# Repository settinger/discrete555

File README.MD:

# VS555

## A 555-style timer made of discrete components, DIP-8 size

Evil Mad Scientist Labs famously [scaled up the 555 timer](https://shop.evilmadscientist.com/productsmenu/652), splitting it into discrete parts. Can it be scaled back down to DIP-8 size, but keeping the discrete parts?

Albert van Dalen created a [wager to shrinkify EMSL's discrete 741 op-amp](https://www.avdweb.nl/div/misc2/discrete-741-operational-amplifier-in-dil8). Additional info on [hackaday.io](https://hackaday.io/project/177194-discrete-741-operational-amplifier-in-dil8). My approach to that challenge is [here](https://github.com/settinger/discrete741). It seemed only natural to extend it to EMSL's 555 kit, also!

The discrete 555 IC has 6 more transistors than the discrete 741 IC, so I didn't even try for a one-sided component layout. I had to use 4 layers, as well. The BJTs are in the SOT-883L package (1.0mm by 0.6mm, a wee bit wider than an 0402 component). There are probably some more space savings to be gained by finding a cleverer part arrangement and by switching from KiCad's 0201 footprint to a more compact 0201 footprint.

TODO: Re-check design, order boards and parts if I'm feeling brave, order stencil if I'm not feeling _that_ brave, figure out how a nifty demo.

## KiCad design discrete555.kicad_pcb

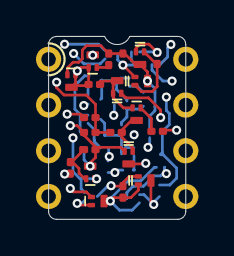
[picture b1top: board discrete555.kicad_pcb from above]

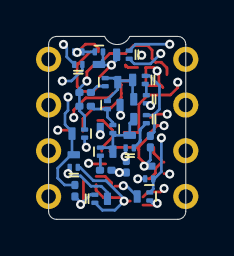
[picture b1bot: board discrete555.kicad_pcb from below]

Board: 4 copper layers, 7.6 x 10.2 mm, 44 parts (22 on the bottom side), 33 nets.

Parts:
J1: DIP-8; DIP-8_W7.62mm
Q1, Q2, Q3, Q4, Q14, Q15, Q16, Q17, Q18, Q20, Q21, Q22, Q24: CET3904E; SOT-883L-alt
Q5, Q6, Q7, Q8, Q9, Q10, Q11, Q12, Q13, Q23, Q25, Q191, Q192: CET3906E; SOT-883L
R1, R3, R7, R8, R9, R11, R15: 4.7kΩ; R_0201_0603Metric
R2: 820Ω; R_0201_0603Metric
R4: 1kΩ; R_0201_0603Metric
R5: 10kΩ; R_0201_0603Metric
R6, R17: 100kΩ; R_0201_0603Metric
R10: 15kΩ; R_0201_0603Metric
R12: 6.8kΩ; R_0201_0603Metric
R13: 3.9kΩ; R_0201_0603Metric
R14: 220Ω; R_0201_0603Metric
R16: 100Ω; R_0201_0603Metric

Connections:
CTRL: J1.5, Q4.1, R7.2, R8.1
DIS: J1.7, Q14.3
GND: J1.1, Q7.3, Q10.3, Q12.3, Q13.3, Q14.2, Q15.2, Q16.2, Q17.2, Q24.2, R5.2, R6.2, R9.2, R15.2
unnamed: Q1.2, Q2.1
unnamed: Q1.3, Q2.3, Q5.1, Q5.3, Q6.1
unnamed: Q2.2, Q3.2, R5.1
unnamed: Q3.1, Q4.2
unnamed: Q3.3, Q4.3, Q7.1, Q8.1, Q8.3
unnamed: Q5.2, R1.2
unnamed: Q6.2, Q7.2, R2.2
unnamed: Q8.2, R3.2
unnamed: Q9.2, R4.2
unnamed: Q10.2, Q11.1
unnamed: Q9.3, Q11.2, Q12.2
unnamed: Q11.3, Q15.1, R6.1
unnamed: Q12.1, Q13.2
unnamed: Q13.1, R8.2, R9.1
unnamed: Q14.1, Q25.3, R16.2
unnamed: Q6.3, Q15.3, Q16.1, R11.2
unnamed: Q16.3, Q17.1, Q18.2
unnamed: Q17.3, Q20.1, Q191.3, R11.1
unnamed: Q18.1, Q18.3, Q25.2, R10.2
unnamed: Q20.2, R14.2, R15.1, R16.1
unnamed: Q20.3, Q21.1, Q23.1, Q23.3, R12.1
unnamed: Q21.2, Q22.1, R13.2
unnamed: Q24.1, R14.1
unnamed: Q25.1, R17.2
unnamed: Q9.1, Q191.1, Q192.1, Q192.3, R10.1
OUT: J1.3, Q22.2, Q23.2, Q24.3, R13.1
THR: J1.6, Q1.1
TRIG: J1.2, Q10.1
Vcc: J1.8, Q21.3, Q22.3, Q191.2, Q192.2, R1.1, R2.1, R3.1, R4.1, R7.1, R12.2
~RST: J1.4, R17.1

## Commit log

2021-10-04 Init commit
2021-10-04 Fussed with top placement a bit more
2021-10-04 Added divot indicator, gotta have a divot indicator
